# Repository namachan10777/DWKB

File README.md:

# DWKB

Depression Working Keyboard.

## Build firmware

```sh
cd soft
cargo build --release --target=thumbv7em-none-eabihf
```

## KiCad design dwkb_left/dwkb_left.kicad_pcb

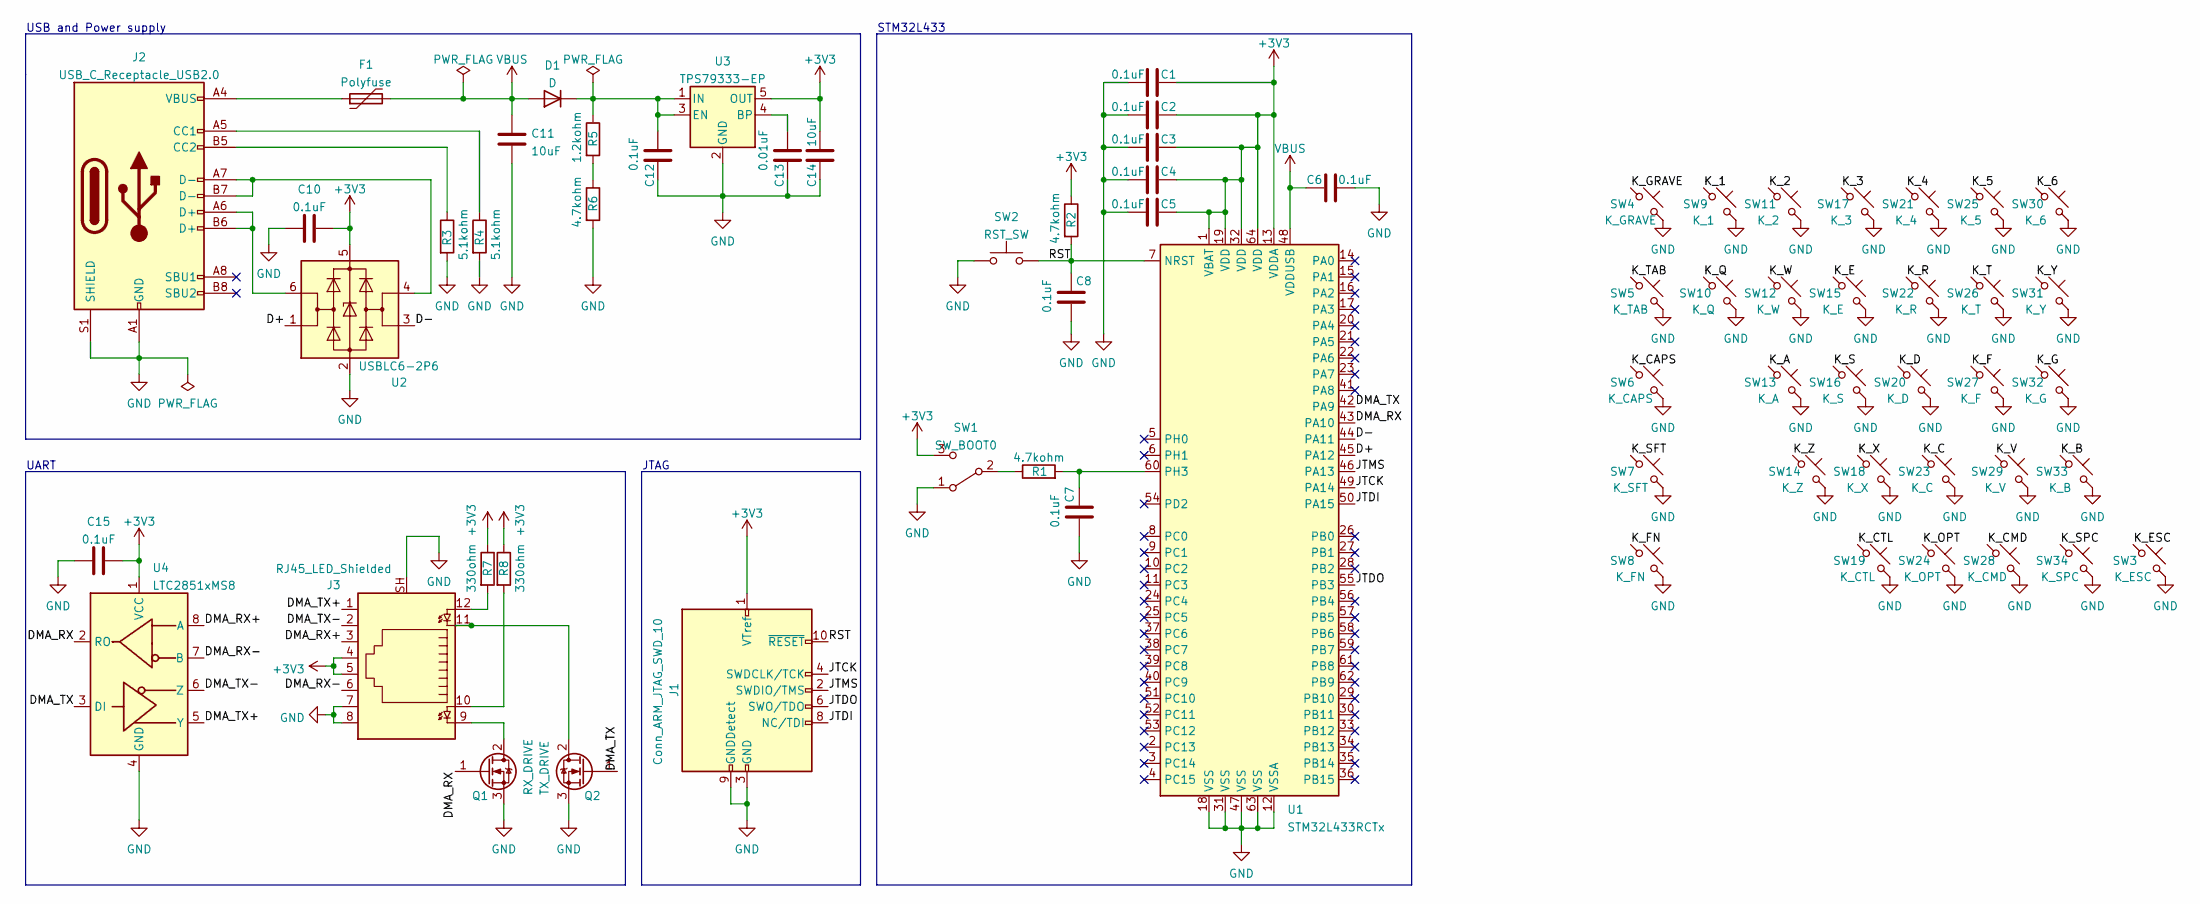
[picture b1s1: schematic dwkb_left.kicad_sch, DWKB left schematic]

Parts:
C1, C2, C3, C4, C5, C6, C7, C8, C10, C12, C15: 0.1uF; C_0603_1608Metric_Pad1.08x0.95mm_HandSolder
C11: 10uF; C_0603_1608Metric_Pad1.08x0.95mm_HandSolder
C13: 0.01uF; C_0603_1608Metric_Pad1.08x0.95mm_HandSolder
C14: 10uF; C_1206_3216Metric_Pad1.33x1.80mm_HandSolder
D1: D; D_SOD-123
F1: Polyfuse; Fuse_0805_2012Metric_Pad1.15x1.40mm_HandSolder
J1: Conn_ARM_JTAG_SWD_10; PinHeader_2x05_P1.27mm_Vertical
J2: USB_C_Receptacle_USB2.0; USB_C_Receptacle_Palconn_UTC16-G
J3: RJ45_LED_Shielded; RJ45_BEL_SS74301-00x_Vertical
Q1: RX_DRIVE; SOT-23
Q2: TX_DRIVE; SOT-23
R1, R2, R6: 4.7kohm; R_0603_1608Metric_Pad0.98x0.95mm_HandSolder
R3, R4: 5.1kohm; R_0603_1608Metric_Pad0.98x0.95mm_HandSolder
R5: 1.2kohm; R_0603_1608Metric_Pad0.98x0.95mm_HandSolder
R7, R8: 330ohm; R_0603_1608Metric_Pad0.98x0.95mm_HandSolder
SW1: SW_BOOT0; SW_SPDT_PCM12
SW2: RST_SW; SW_SPST_PTS810
SW3: K_ESC; Kailh_Choc_V2_1.00u_PCB
SW4: K_GRAVE; Kailh_Choc_V2_1.00u_PCB
SW5: K_TAB; Kailh_Choc_V2_1.50u_PCB
SW6: K_CAPS; Kailh_Choc_V2_1.75u_PCB
SW7: K_SFT; Kailh_Choc_V2_2.25u_PCB
SW8: K_FN; Kailh_Choc_V2_1.00u_PCB
SW9: K_1; Kailh_Choc_V2_1.00u_PCB
SW10: K_Q; Kailh_Choc_V2_1.00u_PCB
SW11: K_2; Kailh_Choc_V2_1.00u_PCB
SW12: K_W; Kailh_Choc_V2_1.00u_PCB
SW13: K_A; Kailh_Choc_V2_1.00u_PCB
SW14: K_Z; Kailh_Choc_V2_1.00u_PCB
SW15: K_E; Kailh_Choc_V2_1.00u_PCB
SW16: K_S; Kailh_Choc_V2_1.00u_PCB
SW17: K_3; Kailh_Choc_V2_1.00u_PCB
SW18: K_X; Kailh_Choc_V2_1.00u_PCB
SW19: K_CTL; Kailh_Choc_V2_1.25u_PCB
SW20: K_D; Kailh_Choc_V2_1.00u_PCB
SW21: K_4; Kailh_Choc_V2_1.00u_PCB
SW22: K_R; Kailh_Choc_V2_1.00u_PCB
SW23: K_C; Kailh_Choc_V2_1.00u_PCB
SW24: K_OPT; Kailh_Choc_V2_1.25u_PCB
SW25: K_5; Kailh_Choc_V2_1.00u_PCB
SW26: K_T; Kailh_Choc_V2_1.00u_PCB
SW27: K_F; Kailh_Choc_V2_1.00u_PCB
SW28: K_CMD; Kailh_Choc_V2_1.25u_PCB
SW29: K_V; Kailh_Choc_V2_1.00u_PCB
SW30: K_6; Kailh_Choc_V2_1.00u_PCB
SW31: K_Y; Kailh_Choc_V2_1.00u_PCB
SW32: K_G; Kailh_Choc_V2_1.00u_PCB
SW33: K_B; Kailh_Choc_V2_1.00u_PCB
SW34: K_SPC; Kailh_Choc_V2_1.50u_PCB
U1: STM32L433RCTx; LQFP-64_10x10mm_P0.5mm
U2: USBLC6-2P6; SOT-666
U3: TPS79333-EP; SOT-23-5
U4: LTC2851xMS8; MSOP-8_3x3mm_P0.65mm

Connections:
+3V3: C1.1, C2.1, C3.1, C4.1, C5.1, C10.2, C14.1, C15.2, J1.1 (VTref), J3.4, J3.5, R2.1, R7.1, R8.1, SW1.3 (C), U1.1 (VBAT), U1.13 (VDDA), U1.19 (VDD), U1.32 (VDD), U1.64 (VDD), U2.5 (VBUS), U3.5 (OUT), U4.1 (VCC)
/D+: U1.45 (PA12), U2.1 (I/O1)
/D-: U1.44 (PA11), U2.3 (I/O2)
/DMA_RX: Q1.1 (G), U1.43 (PA10), U4.2 (RO)
/DMA_RX+: J3.3, U4.8 (A)
/DMA_RX-: J3.6, U4.7 (B)
/DMA_TX: Q2.1 (G), U1.42 (PA9), U4.3 (DI)
/DMA_TX+: J3.1, U4.5 (Y)
/DMA_TX-: J3.2, U4.6 (Z)
/JTCK: J1.4 (SWDCLK/TCK), U1.49 (PA14)
/JTDI: J1.8 (NC/TDI), U1.50 (PA15)
/JTDO: J1.6 (SWO/TDO), U1.55 (PB3)
/JTMS: J1.2 (SWDIO/TMS), U1.46 (PA13)
/K_1: SW9.1
/K_2: SW11.1
/K_3: SW17.1
/K_4: SW21.1
/K_5: SW25.1
/K_6: SW30.1
/K_A: SW13.1
/K_B: SW33.1
/K_C: SW23.1
/K_CAPS: SW6.1
/K_CMD: SW28.1
/K_CTL: SW19.1
/K_D: SW20.1
/K_E: SW15.1
/K_ESC: SW3.1
/K_F: SW27.1
/K_FN: SW8.1
/K_G: SW32.1
/K_GRAVE: SW4.1
/K_OPT: SW24.1
/K_Q: SW10.1
/K_R: SW22.1
/K_S: SW16.1
/K_SFT: SW7.1
/K_SPC: SW34.1
/K_T: SW26.1
/K_TAB: SW5.1
/K_V: SW29.1
/K_W: SW12.1
/K_X: SW18.1
/K_Y: SW31.1
/K_Z: SW14.1
/RST: C8.1, J1.10 (~RESET), R2.2, SW2.2, U1.7 (NRST)
GND: C1.2, C2.2, C3.2, C4.2, C5.2, C6.2, C7.2, C8.2, C10.1, C11.2, C12.2, C13.2, C14.2, C15.1, J1.3 (GND), J1.5 (GND), J1.9 (GNDDetect), J2.A1 (GND), J2.A12 (GND), J2.B1 (GND), J2.B12 (GND), J2.S1 (SHIELD), J3.7, J3.8, J3.SH, Q1.3 (S), Q2.3 (S), R3.2, R4.2, R6.2, SW1.1 (A), SW2.1, SW3.2, SW4.2, SW5.2, SW6.2, SW7.2, SW8.2, SW9.2, SW10.2, SW11.2, SW12.2, SW13.2, SW14.2, SW15.2, SW16.2, SW17.2, SW18.2, SW19.2, SW20.2, SW21.2, SW22.2, SW23.2, SW24.2, SW25.2, SW26.2, SW27.2, SW28.2, SW29.2, SW30.2, SW31.2, SW32.2, SW33.2, SW34.2, U1.12 (VSSA), U1.18 (VSS), U1.31 (VSS), U1.47 (VSS), U1.63 (VSS), U2.2 (GND), U3.2 (GND), U4.4 (GND)
unnamed: C7.1, R1.2, U1.60 (PH3)
unnamed: C12.1, D1.1 (K), R5.1, U3.1 (IN), U3.3 (EN)
unnamed: C13.1, U3.4 (BP)
unnamed: F1.1, J2.A4 (VBUS), J2.A9 (VBUS), J2.B4 (VBUS), J2.B9 (VBUS)
unnamed: J2.A5 (CC1), R4.1
unnamed: J2.A6 (D+), J2.B6 (D+), U2.6 (I/O1)
unnamed: J2.A7 (D-), J2.B7 (D-), U2.4 (I/O2)
unnamed: J2.B5 (CC2), R3.1
unnamed: J3.9, Q1.2 (D)
unnamed: J3.10, R8.2
unnamed: J3.11, Q2.2 (D)
unnamed: J3.12, R7.2
unnamed: R1.1, SW1.2 (B)
unnamed: R5.2, R6.1
VBUS: C6.1, C11.1, D1.2 (A), F1.2, U1.48 (VDDUSB)

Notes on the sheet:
STM32L433
USB and Power supply
UART
JTAG

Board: 2 copper layers, 67 parts (0 on the bottom side), 30 nets, no tracks yet.

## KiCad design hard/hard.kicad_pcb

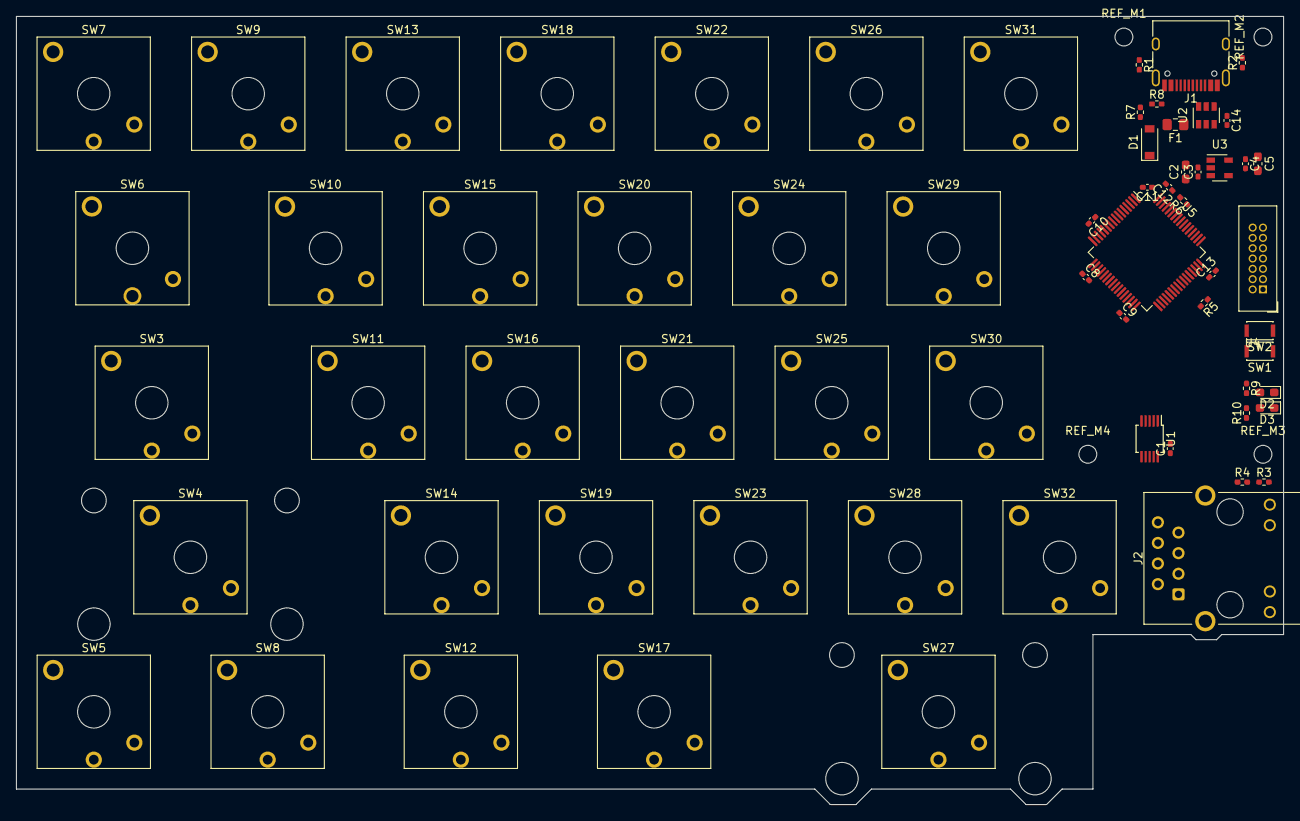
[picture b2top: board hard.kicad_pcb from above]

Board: 2 copper layers, 156.2 x 97.2 mm, 69 parts (0 on the bottom side), 62 nets, no tracks yet.

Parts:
C1, C3, C4, C8, C9, C10, C11, C12, C13, C14: 0.1uF; C_0402_1005Metric_Pad0.74x0.62mm_HandSolder
C2, C5: 1uF; C_0603_1608Metric_Pad1.08x0.95mm_HandSolder
D1: D; D_SOD-123
D2: STATUS1; LED_0603_1608Metric_Pad1.05x0.95mm_HandSolder
D3: STATUS2; LED_0603_1608Metric_Pad1.05x0.95mm_HandSolder
F1: Polyfuse; Fuse_0805_2012Metric_Pad1.15x1.40mm_HandSolder
J1: USB_C_Receptacle_USB2.0; USB_C_Receptacle_HRO_TYPE-C-31-M-12
J2: RJ45_LED_Shielded; RJ45_Hanrun_HR911105A
R1, R2: 5.1kOhm; R_0402_1005Metric_Pad0.72x0.64mm_HandSolder
R3, R4: R; R_0402_1005Metric_Pad0.72x0.64mm_HandSolder
R5, R6: 4.7kOhm; R_0402_1005Metric_Pad0.72x0.64mm_HandSolder
R7: 2.2kOhm; R_0402_1005Metric_Pad0.72x0.64mm_HandSolder
R8: 3.3kOhm; R_0402_1005Metric_Pad0.72x0.64mm_HandSolder
R9, R10: 330Ohm; R_0402_1005Metric_Pad0.72x0.64mm_HandSolder
REF_M1, REF_M2, REF_M3, REF_M4: MountingHole_2.2mm_M2_DIN965
SW1: SW_RST; SW_SPST_CK_KXT3
SW2: SW_BOOT0; SW_SPST_CK_KXT3
SW3: KEY_CAPSLOCK; Kailh_Choc_V2_1.75u_PCB
SW4: KEY_LSHIFT; Kailh_Choc_V2_2.25u_PCB
SW5: KEY_LFN; Kailh_Choc_V2_1.00u_PCB
SW6: KEY_TAB; Kailh_Choc_V2_1.50u_PCB
SW7: KEY_ESCAPE; Kailh_Choc_V2_1.00u_PCB
SW8: KEY_CONTROL; Kailh_Choc_V2_1.25u_PCB
SW9: KEY_1; Kailh_Choc_V2_1.00u_PCB
SW10: KEY_Q; Kailh_Choc_V2_1.00u_PCB
SW11: KEY_A; Kailh_Choc_V2_1.00u_PCB
SW12: KEY_OPTION; Kailh_Choc_V2_1.25u_PCB
SW13: KEY_2; Kailh_Choc_V2_1.00u_PCB
SW14: KEY_Z; Kailh_Choc_V2_1.00u_PCB
SW15: KEY_W; Kailh_Choc_V2_1.00u_PCB
SW16: KEY_S; Kailh_Choc_V2_1.00u_PCB
SW17: KEY_COMMAND; Kailh_Choc_V2_1.25u_PCB
SW18: KEY_3; Kailh_Choc_V2_1.00u_PCB
SW19: KEY_X; Kailh_Choc_V2_1.00u_PCB
SW20: KEY_E; Kailh_Choc_V2_1.00u_PCB
SW21: KEY_D; Kailh_Choc_V2_1.00u_PCB
SW22: KEY_4; Kailh_Choc_V2_1.00u_PCB
SW23: KEY_C; Kailh_Choc_V2_1.00u_PCB
SW24: KEY_R; Kailh_Choc_V2_1.00u_PCB
SW25: KEY_F; Kailh_Choc_V2_1.00u_PCB
SW26: KEY_5; Kailh_Choc_V2_1.00u_PCB
SW27: KEY_SPACE; Kailh_Choc_V2_2.00u_PCB
SW28: KEY_V; Kailh_Choc_V2_1.00u_PCB
SW29: KEY_T; Kailh_Choc_V2_1.00u_PCB
SW30: KEY_G; Kailh_Choc_V2_1.00u_PCB
SW31: KEY_6; Kailh_Choc_V2_1.00u_PCB
SW32: KEY_B; Kailh_Choc_V2_1.00u_PCB
U1: LTC2852xMS; MSOP-10_3x3mm_P0.5mm
U2: USBLC6-2SC6; SOT-23-6
U3: MIC5504-3.3YM5; SOT-23-5
U4: STLinkV3; IDC-Header_2x07_P1.27mm_Vertical
U5: STM32L412RBTx; LQFP-64_10x10mm_P0.5mm

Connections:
+3V3: C1.1, C4.1, C5.1, C8.2, C9.2, C10.2, C11.2, C12.2, C13.2, R5.1, R9.1, R10.1, SW2.1, U1.3, U1.10, U3.5, U4.3, U5.1, U5.13, U5.19, U5.32, U5.48, U5.64
/D+: U2.1, U5.45
/D-: U2.3, U5.44
/ETH_RX+: J2.6, U1.9
/ETH_RX-: J2.3, U1.8
/ETH_TX+: J2.2, U1.7
/ETH_TX-: J2.1, U1.6
/JTCK: U4.6, U4.9, U5.49
/JTDI: U4.10, U5.50
/JTDO: U4.8, U5.54
/JTMS: U4.4, U5.46
/KEY_1: SW9.2, U5.21
/KEY_2: SW13.2, U5.22
/KEY_3: SW18.2, U5.23
/KEY_4: SW22.2, U5.40
/KEY_5: SW26.2, U5.39
/KEY_6: SW31.2, U5.38
/KEY_A: SW11.2, U5.8
/KEY_B: SW32.2, U5.2
/KEY_C: SW23.2, U5.52
/KEY_CAPSLOCK: SW3.2, U5.37
/KEY_COMMAND: SW17.2, U5.35
/KEY_CONTROL: SW8.2, U5.27
/KEY_D: SW21.2, U5.10
/KEY_E: SW20.2, U5.29
/KEY_ESCAPE: SW7.2, U5.20
/KEY_F: SW25.2, U5.11
/KEY_G: SW30.2, U5.60
/KEY_LFN: SW5.2, U5.26
/KEY_LSHIFT: SW4.2, U5.25
/KEY_OPTION: SW12.2, U5.34
/KEY_Q: SW10.2, U5.51
/KEY_R: SW24.2, U5.55
/KEY_S: SW16.2, U5.9
/KEY_SPACE: SW27.2, U5.36
/KEY_T: SW29.2, U5.56
/KEY_TAB: SW6.2, U5.24
/KEY_V: SW28.2, U5.53
/KEY_W: SW15.2, U5.28
/KEY_X: SW19.2, U5.41
/KEY_Z: SW14.2, U5.33
/NRST: R5.2, SW1.2, U4.12, U5.7
/RX: J2.10, U1.1, U5.43
/TX: J2.12, U1.4, U5.42
/VBUS_DETECT: R7.2, R8.1, U5.3
/VPC_RX: U4.14, U5.17
/VPC_TX: U4.13, U5.16
/V_SHARED: C2.1, C3.1, D1.1, J2.4, J2.5, U3.1, U3.3
GND: C1.2, C2.2, C3.2, C4.2, C5.2, C8.1, C9.1, C10.1, C11.1, C12.1, C13.1, C14.2, J1.A1, J1.A12, J1.B1, J1.B12, J1.S1, J2.7, J2.8, J2.SH, R1.2, R2.2, R3.1, R4.1, R6.2, R8.2, SW1.1, SW3.1, SW4.1, SW5.1, SW6.1, SW7.1, SW8.1, SW9.1, SW10.1, SW11.1, SW12.1, SW13.1, SW14.1, SW15.1, SW16.1, SW17.1, SW18.1, SW19.1, SW20.1, SW21.1, SW22.1, SW23.1, SW24.1, SW25.1, SW26.1, SW27.1, SW28.1, SW29.1, SW30.1, SW31.1, SW32.1, U1.2, U1.5, U2.2, U3.2, U4.5, U4.7, U4.11, U5.12, U5.18, U5.31, U5.47, U5.63
unnamed: C14.1, D1.2, F1.1, R7.1, U2.5
unnamed: D2.1, U5.57
unnamed: D2.2, R9.2
unnamed: D3.1, U5.58
unnamed: D3.2, R10.2
unnamed: F1.2, J1.A4, J1.A9, J1.B4, J1.B9
unnamed: J1.A5, R2.1
unnamed: J1.A6, J1.B6, U2.6
unnamed: J1.A7, J1.B7, U2.4
unnamed: J1.B5, R1.1
unnamed: J2.9, R3.2
unnamed: J2.11, R4.2
unnamed: R6.1, SW2.2, U5.59

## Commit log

2021-08-31 init
2021-08-31 place keys on sch
2021-08-31 wiring keys
2021-08-31 GHA rust
2021-08-31 cargo clippy and fmt --check on GHA
2021-08-31 labeling net
2021-08-31 assign Diode footprints
2021-09-01 essential configuration for STM32F401RET6
2021-09-01 add RJ45 x2
2021-09-02 rename to dwkb
2021-09-14 Kailh Choc V2 footprints
2021-09-14 sch: WIP
2021-09-14 add Kailh Choc V2 key
2021-09-14 assign key footprints
2021-09-14 place keys
2021-09-14 assign all footprints
2021-09-15 draw outline
2021-09-15 set all footprints
2021-10-09 STM32L412RBTx
2021-10-09 misc circuits
2021-11-10 gen2
2021-11-10 cargo
2021-11-10 kicad automated
2021-11-10 cannot connect
2021-11-10 run only check
2021-11-10 fix kibot config name
2021-11-10 soft: hello world
2021-11-10 hard: new shape
2021-11-10 THVD1451D -> THVD1452
2021-11-16 termination resister
2021-11-17 fix termination resister
2021-12-13 kicad 6
